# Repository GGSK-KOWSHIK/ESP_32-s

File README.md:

## Project Summary:4 Layers Custom IoT PCB with ESP32-C3-02.

This project involves the design and development of a **4-layer custom PCB** for an IoT application powered by the ESP32-C3-02 SoC. The board integrates **Wi-Fi/BLE connectivity** and **TP4056-based Li-ion charging circuitry**, enabling efficient and safe charging of a single-cell Li-ion battery.

### Key Features

- **Microcontroller**: ESP32-C3-02 SoC with Wi-Fi and BLE connectivity  
- **Power Management**: TP4056 IC for single-cell Li-ion battery charging with thermal regulation  
- **Battery Protection**: Integrated under-voltage lockout and trickle charging  
- **Sensors and Modules**:  
  - BME280 for temperature, humidity, and pressure sensing  
  - Ambient light and sound sensors  
  - Mini SD card reader for local data storage  
  - Onboard flash memory for extended storage  
- **Display**: I2C OLED for real-time data visualization  
- **Power Inputs**:  
  - USB-C connector for charging and data transfer  
  - LiPo battery connector with onboard charging circuitry  
- **Indicators**: LED indicators showing charging and full-charge status  

### Design Highlights

1. **Power Supply Integration**  
   - USB-C powers both charging and system operation  
   - TP4056 manages charging and protection  
   - Regulated supply ensures ESP32-C3-02 stability  

2. **Modular Architecture**  
   - Supports multiple onboard sensors  
   - Expandable via additional I2C devices  

3. **Safe and Efficient Charging**  
   - Programmable charging current (external resistor)  
   - Automatic charge termination and built-in protection  

4. **Compact and Reliable Layout**  
   - Optimized **4-layer PCB routing** for minimal power loss  
   - Thermal management for TP4056 and critical components  

### Applications

- IoT edge devices for environmental monitoring  
- Low-power battery-operated data logging systems  
- Prototyping platform for ESP32-based IoT solutions

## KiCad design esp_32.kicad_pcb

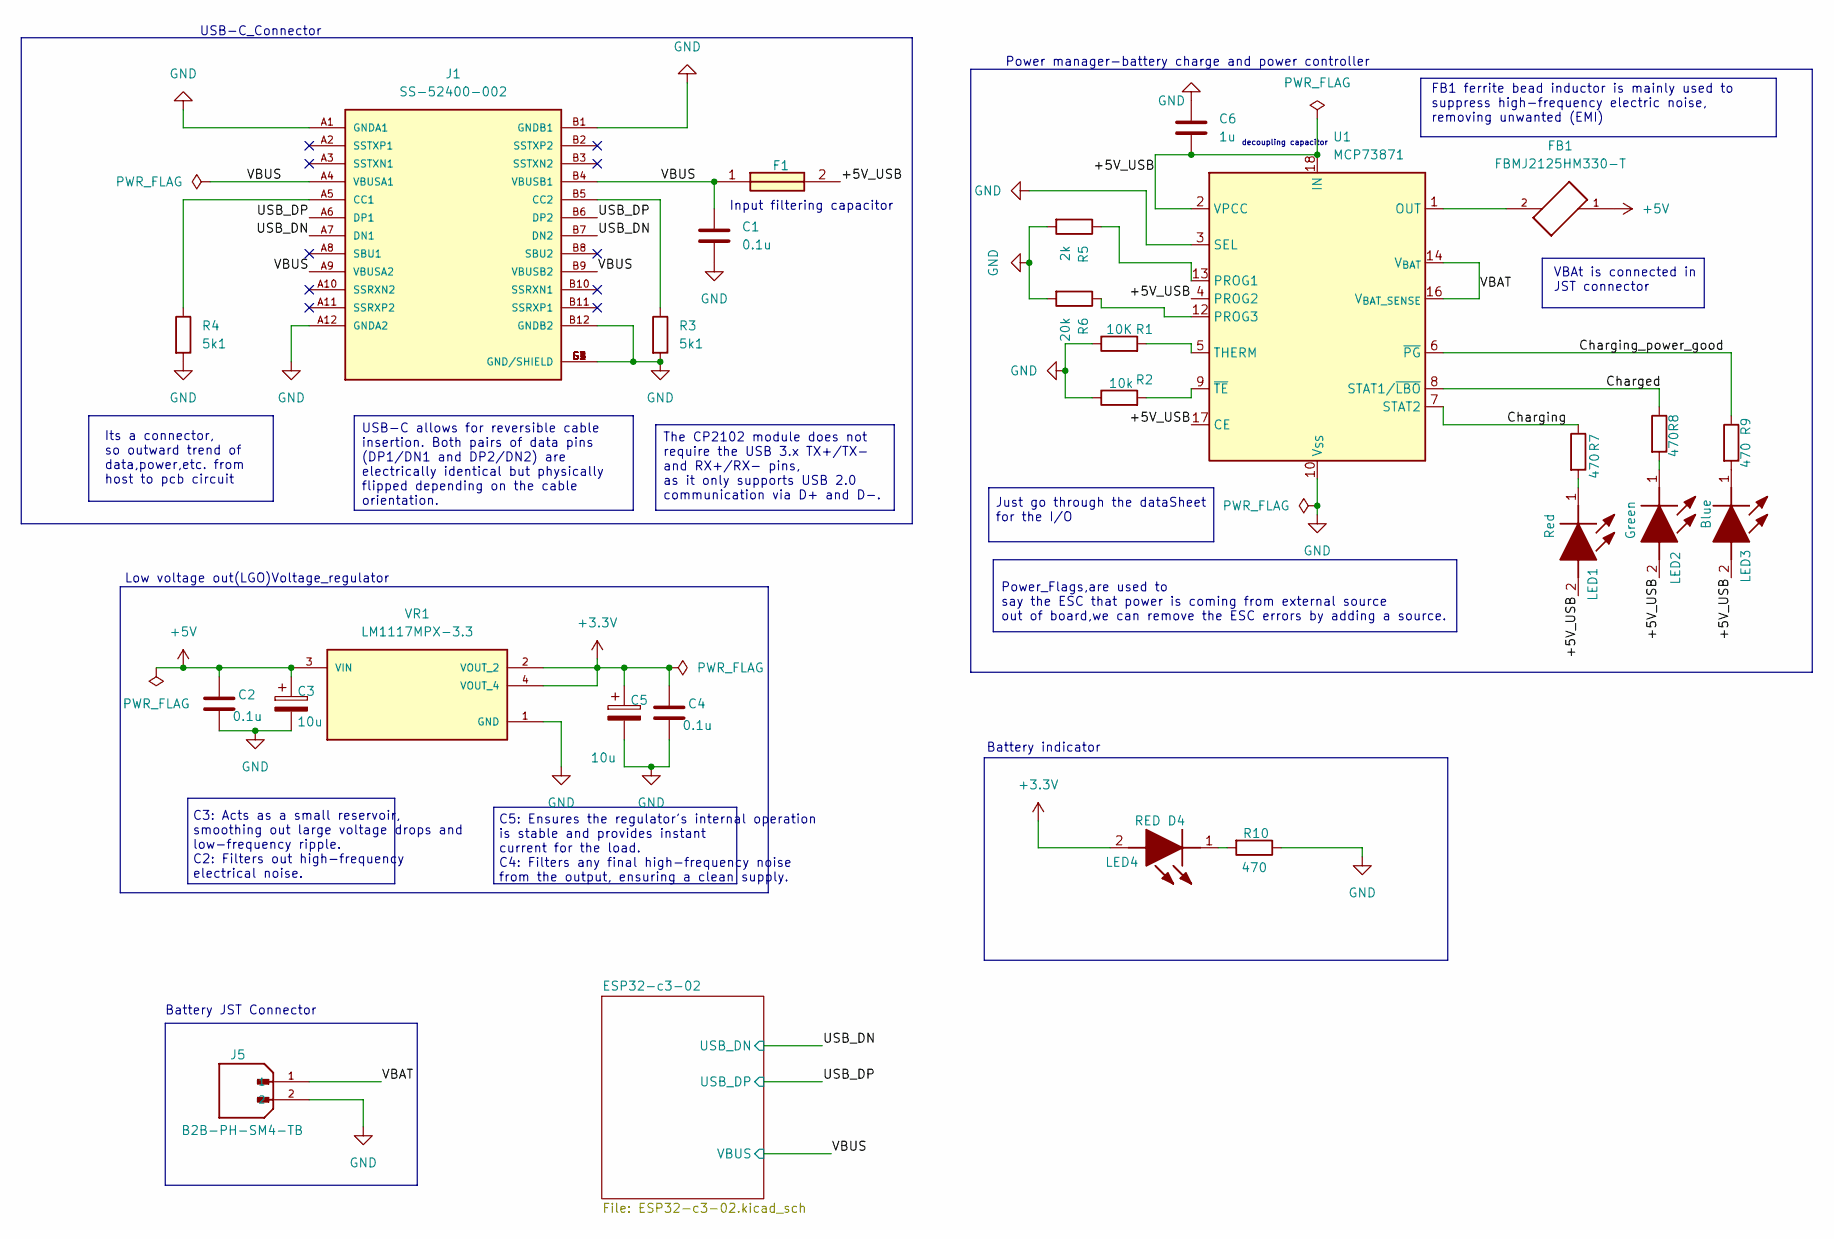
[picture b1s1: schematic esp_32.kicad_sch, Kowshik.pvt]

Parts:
C1, C2, C4: 0.1u; C_0805_2012Metric
C3, C5: 10u; T491A
C6: 1u; C_0805_2012Metric
F1: 0ZCH0110AF2E; FUSC3226X100N; Manufacturer_Part_Number 0ZCH0110AF2E
FB1: FBMJ2125HM330-T; BEADC2012X105N
J1: SS-52400-002; BELFUSE_SS-52400-002; PARTREV A0
J5: B2B-PH-SM4-TB; JST_PH_B2B-PH-K_1x02_P2.00mm_Vertical; PARTREV N/A
LED1: Red; LEDC2012X120N; Manufacturer_Part_Number LTST-C170KRKT; Mouser Part Number 859-LTST-C170KRKT
LED2: Green; LEDC2012X120N; Manufacturer_Part_Number LTST-C170GKT; Mouser Part Number 859-LTST-C170GKT
LED3: Blue; LEDC2012X120N; Manufacturer_Part_Number LTST-C170TBKT; Mouser Part Number 859-LTST-C170TBKT
LED4: RED D4; LEDC2012X120N; Manufacturer_Part_Number LTST-C170KRKT; Mouser Part Number 859-LTST-C170KRKT
R1: 10K; R_0805_2012Metric
R2: 10k; R_0805_2012Metric
R3, R4: 5k1; R_0805_2012Metric
R5: 2k; R_0805_2012Metric
R6: 20k; R_0805_2012Metric
R7, R8, R9, R10: 470; R_0805_2012Metric
U1: MCP73871; QFN-20-1EP_4x4mm_P0.5mm_EP2.5x2.5mm
VR1: LM1117MPX-3.3; VREG_LM1117MPX-3.3

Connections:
+3.3V: C4.1, C5.1, LED4.2 (A), VR1.2 (VOUT_2), VR1.4 (VOUT_4); also elsewhere on the board
+5V: C2.1, C3.1, FB1.1, VR1.3 (VIN)
/+5V_USB: C6.2, F1.2, LED1.2 (A), LED2.2 (A), LED3.2 (A), U1.2 (VPCC), U1.4 (PROG2), U1.17 (CE), U1.18 (IN), U1.19 (IN)
/Charged: R8.1, U1.8 (STAT1/~LBO)
/Charging: R7.1, U1.7 (STAT2)
/Charging_power_good: R9.1, U1.6 (~PG)
/USB_DN: J1.A7 (DN1), J1.B7 (DN2); also elsewhere on the board
/USB_DP: J1.A6 (DP1), J1.B6 (DP2); also elsewhere on the board
/VBAT: J5.1, U1.14 (V_{BAT}), U1.15 (V_{BAT}), U1.16 (V_{BAT_SENSE})
/VBUS: C1.1, F1.1, J1.A4 (VBUSA1), J1.A9 (VBUSA2), J1.B4 (VBUSB1), J1.B9 (VBUSB2); also elsewhere on the board
GND: C1.2, C2.2, C3.2, C4.2, C5.2, C6.1, J1.A1 (GNDA1), J1.A12 (GNDA2), J1.B1 (GNDB1), J1.B12 (GNDB2), J1.G1 (GND/SHIELD), J1.G2 (GND/SHIELD), J1.G3 (GND/SHIELD), J1.G4 (GND/SHIELD), J1.S1 (GND/SHIELD), J1.S2 (GND/SHIELD), J1.S3 (GND/SHIELD), J1.S4 (GND/SHIELD), J5.2, R1.1, R2.1, R3.2, R4.2, R5.2, R6.2, R10.1, U1.3 (SEL), U1.10 (V_{SS}), U1.11 (V_{SS}), U1.21 (V_{SS}), VR1.1 (GND); also elsewhere on the board
unnamed: FB1.2, U1.1 (OUT), U1.20 (OUT)
unnamed: J1.A5 (CC1), R4.1
unnamed: J1.B5 (CC2), R3.1
unnamed: LED1.1 (K), R7.2
unnamed: LED2.1 (K), R8.2
unnamed: LED3.1 (K), R9.2
unnamed: LED4.1 (K), R10.2
unnamed: R5.1, U1.13 (PROG1)
unnamed: R6.1, U1.12 (PROG3)
unnamed: R1.2, U1.5 (THERM)
unnamed: R2.2, U1.9 (~TE)

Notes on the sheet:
Input filtering capacitor
Power manager-battery charge and power controller
C3: Acts as a small reservoir, smoothing out large voltage drops and low-frequency ripple. C2: Filters out high-frequency electrical noise.
Battery indicator
Low voltage out(LGO)Voltage_regulator
Battery JST Connector
Power_Flags,are used to say the ESC that power is coming from external source out of board,we can remove the ESC errors by adding a source.
VBAt is connected in JST connector
Its a connector, so outward trend of data,power,etc. from host to pcb circuit
C5: Ensures the regulator's internal operation is stable and provides instant current for the load. C4: Filters any final high-frequency noise from the output, ensuring a clean supply.
decoupling capacitor
USB-C_Connector
Just go through the dataSheet for the I/O
FB1 ferrite bead inductor is mainly used to suppress high-frequency electric noise, removing unwanted (EMI)
USB-C allows for reversible cable insertion. Both pairs of data pins (DP1/DN1 and DP2/DN2) are electrically identical but physically flipped depending on the cable orientation.
The CP2102 module does not require the USB 3.x TX+/TX- and RX+/RX- pins, as it only supports USB 2.0 communication via D+ and D-.

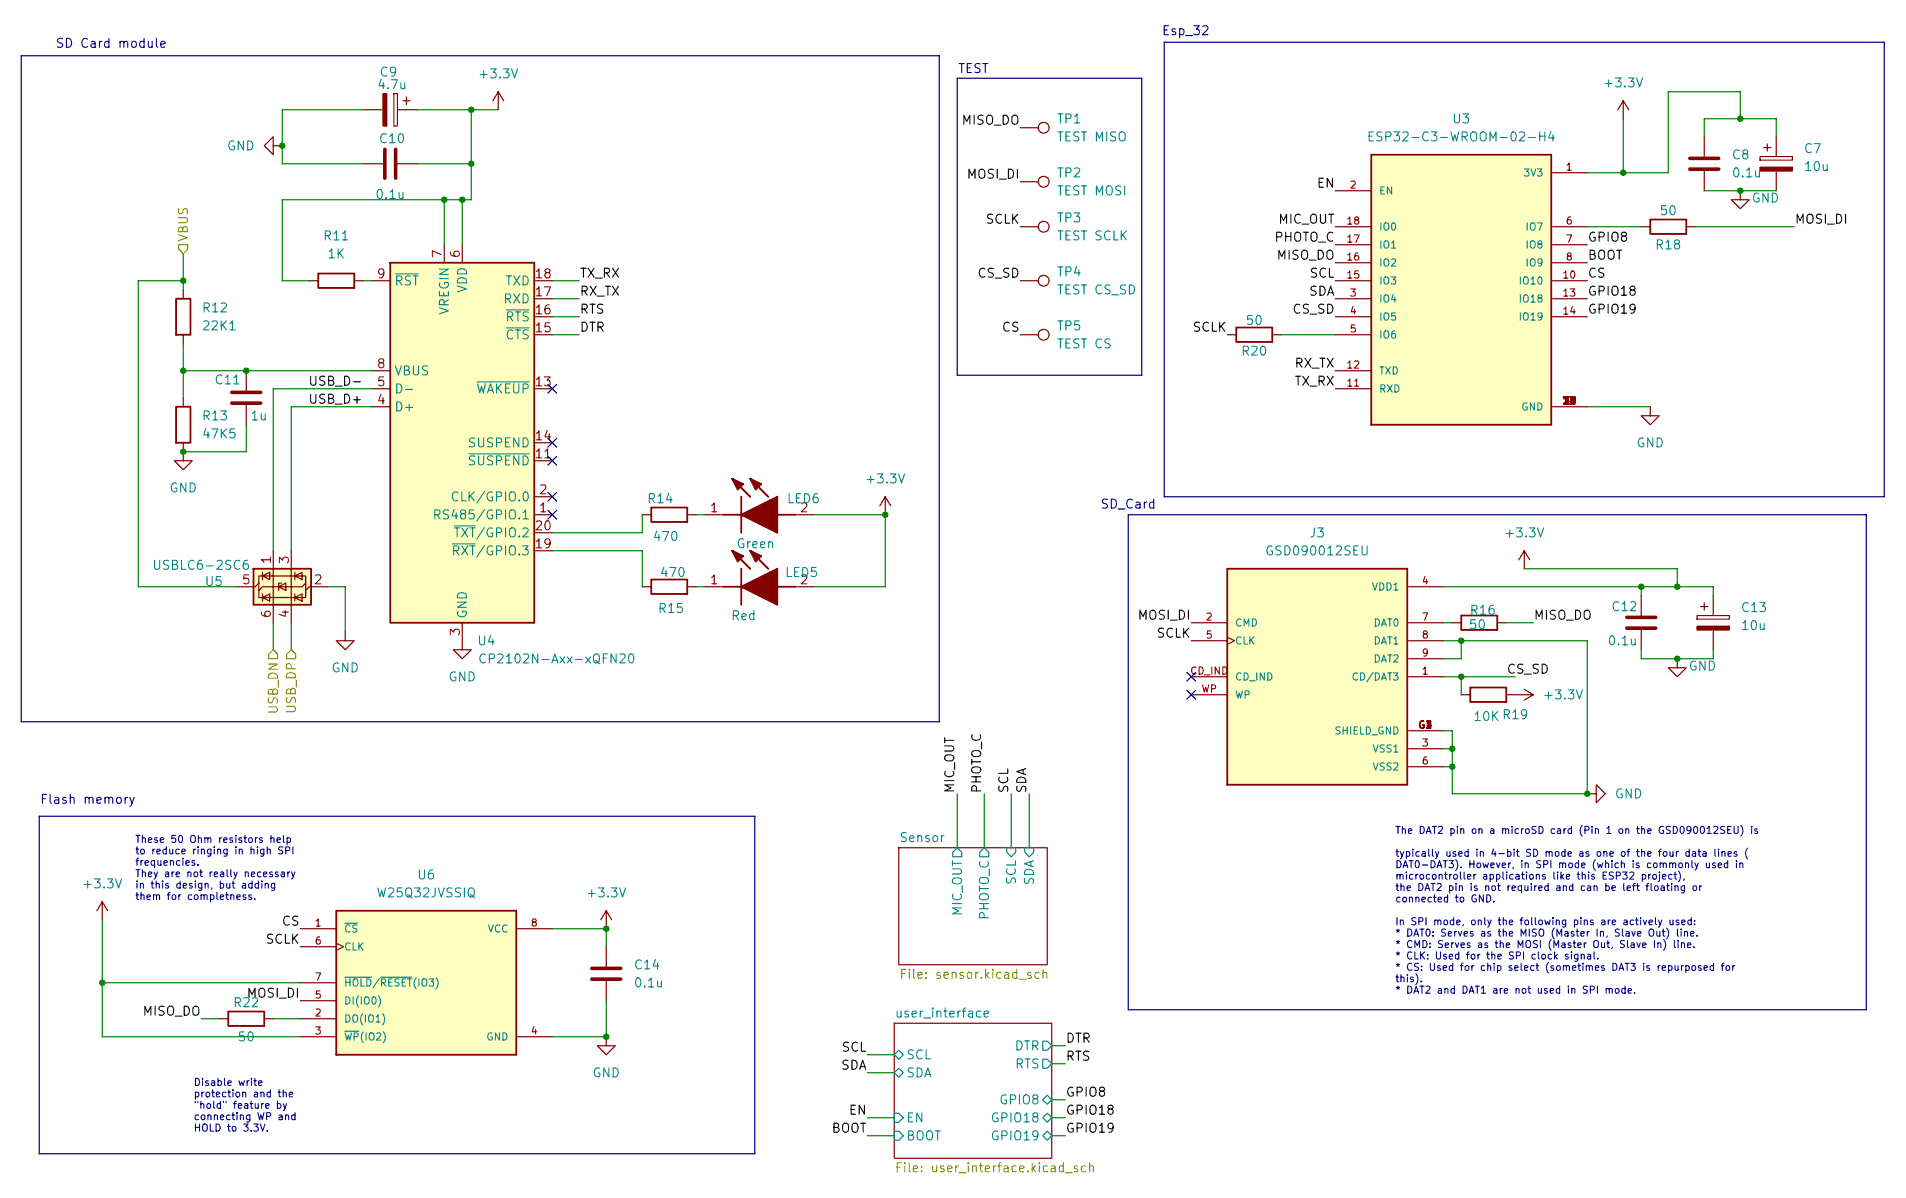
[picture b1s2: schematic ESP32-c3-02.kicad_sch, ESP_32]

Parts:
C7, C13: 10u; T491A
C8, C10, C12, C14: 0.1u; C_0805_2012Metric
C9: 4.7u; T491A
C11: 1u; C_0805_2012Metric
J3: GSD090012SEU; AMPHENOL_GSD090012SEU; PARTREV E
LED5: Red; LEDC2012X120N; Manufacturer_Part_Number LTST-C170KRKT; Mouser Part Number 859-LTST-C170KRKT
LED6: Green; LEDC2012X120N; Manufacturer_Part_Number LTST-C170GKT; Mouser Part Number 859-LTST-C170GKT
R11: 1K; R_0805_2012Metric
R12: 22K1; R_0805_2012Metric
R13: 47K5; R_0805_2012Metric
R14, R15: 470; R_0805_2012Metric
R16, R18, R20, R22: 50; R_0805_2012Metric
R19: 10K; R_0805_2012Metric
TP1: TEST MISO; TestPoint_Pad_D1.0mm
TP2: TEST MOSI; TestPoint_Pad_D1.0mm
TP3: TEST SCLK; TestPoint_Pad_D1.0mm
TP4: TEST CS_SD; TestPoint_Pad_D1.0mm
TP5: TEST CS; TestPoint_Pad_D1.0mm
U3: ESP32-C3-WROOM-02-H4; MODULE_ESP32-C3-WROOM-02-H4
U4: CP2102N-Axx-xQFN20; SiliconLabs_QFN-20-1EP_3x3mm_P0.5mm_EP1.8x1.8mm
U5: USBLC6-2SC6; SOT-23-6
U6: W25Q32JVSSIQ; SOIC127P790X216-8N; M_PART_NUMBER W25QXX

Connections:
+3.3V: C7.1, C8.1, C9.1, C10.2, C12.1, C13.1, C14.1, J3.4 (VDD1), LED5.2 (A), LED6.2 (A), R11.1, R19.2, U3.1 (3V3), U4.6 (VDD), U4.7 (VREGIN), U6.3 (~WP(IO2)), U6.7 (~HOLD/~RESET(IO3)), U6.8 (VCC); also elsewhere on the board
/ESP32-c3-02/BOOT: U3.8 (IO9); also elsewhere on the board
/ESP32-c3-02/CS: TP5.1, U3.10 (IO10), U6.1 (~CS)
/ESP32-c3-02/CS_SD: J3.1 (CD/DAT3), R19.1, TP4.1, U3.4 (IO5)
/ESP32-c3-02/DTR: U4.15 (~CTS); also elsewhere on the board
/ESP32-c3-02/EN: U3.2 (EN); also elsewhere on the board
/ESP32-c3-02/GPIO8: U3.7 (IO8); also elsewhere on the board
/ESP32-c3-02/GPIO18: U3.13 (IO18); also elsewhere on the board
/ESP32-c3-02/GPIO19: U3.14 (IO19); also elsewhere on the board
/ESP32-c3-02/MIC_OUT: U3.18 (IO0); also elsewhere on the board
/ESP32-c3-02/MISO_DO: R16.2, R22.1, TP1.1, U3.16 (IO2)
/ESP32-c3-02/MOSI_DI: J3.2 (CMD), R18.2, TP2.1, U6.5 (DI(IO0))
/ESP32-c3-02/PHOTO_C: U3.17 (IO1); also elsewhere on the board
/ESP32-c3-02/RTS: U4.16 (~RTS); also elsewhere on the board
/ESP32-c3-02/RX_TX: U3.12 (TXD), U4.17 (RXD)
/ESP32-c3-02/SCL: U3.15 (IO3); also elsewhere on the board
/ESP32-c3-02/SCLK: J3.5 (CLK), R20.1, TP3.1, U6.6 (CLK)
/ESP32-c3-02/SDA: U3.3 (IO4); also elsewhere on the board
/ESP32-c3-02/TX_RX: U3.11 (RXD), U4.18 (TXD)
/ESP32-c3-02/USB_D+: U4.4 (D+), U5.3 (I/O2)
/ESP32-c3-02/USB_D-: U4.5 (D-), U5.1 (I/O1)
/USB_DN: U5.6 (I/O1); also elsewhere on the board
/USB_DP: U5.4 (I/O2); also elsewhere on the board
/VBUS: R12.1, U5.5 (VBUS); also elsewhere on the board
GND: C7.2, C8.2, C9.2, C10.1, C11.2, C12.2, C13.2, C14.2, J3.3 (VSS1), J3.6 (VSS2), J3.8 (DAT1), J3.9 (DAT2), J3.G1 (SHIELD_GND), J3.G2 (SHIELD_GND), J3.G3 (SHIELD_GND), J3.G4 (SHIELD_GND), R13.2, U3.9 (GND), U3.19 (GND), U3.20 (GND), U3.21 (GND), U3.22 (GND), U3.23 (GND), U3.24 (GND), U3.25 (GND), U3.26 (GND), U3.27 (GND), U3.28 (GND), U3.29 (GND), U3.30 (GND), U3.31 (GND), U3.32 (GND), U3.33 (GND), U3.34 (GND), U3.35 (GND), U3.36 (GND), U3.37 (GND), U3.38 (GND), U3.39 (GND), U4.3 (GND), U4.12 (GND), U4.21 (GND), U5.2 (GND), U6.4 (GND); also elsewhere on the board
unnamed: J3.7 (DAT0), R16.1
unnamed: LED5.1 (K), R15.2
unnamed: LED6.1 (K), R14.2
unnamed: R20.2, U3.5 (IO6)
unnamed: R18.1, U3.6 (IO7)
unnamed: C11.1, R12.2, R13.1, U4.8 (VBUS)
unnamed: R11.2, U4.9 (~RST)
unnamed: R15.1, U4.19 (~RXT/GPIO.3)
unnamed: R14.1, U4.20 (~TXT/GPIO.2)
unnamed: R22.2, U6.2 (DO(IO1))

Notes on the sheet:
SD Card module
SD_Card
Esp_32
TEST
Flash memory
These 50 Ohm resistors help to reduce ringing in high SPI frequencies. They are not really necessary in this design, but adding them for completness.
The DAT2 pin on a microSD card (Pin 1 on the GSD090012SEU) is typically used in 4-bit SD mode as one of the four data lines ( DAT0-DAT3). However, in SPI mode (which is commonly used in microcontroller applications like this ESP32 project), the DAT2 pin is not required and can be left floating or c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
Disable write protection and the "hold" feature by connecting WP and HOLD to 3.3V.

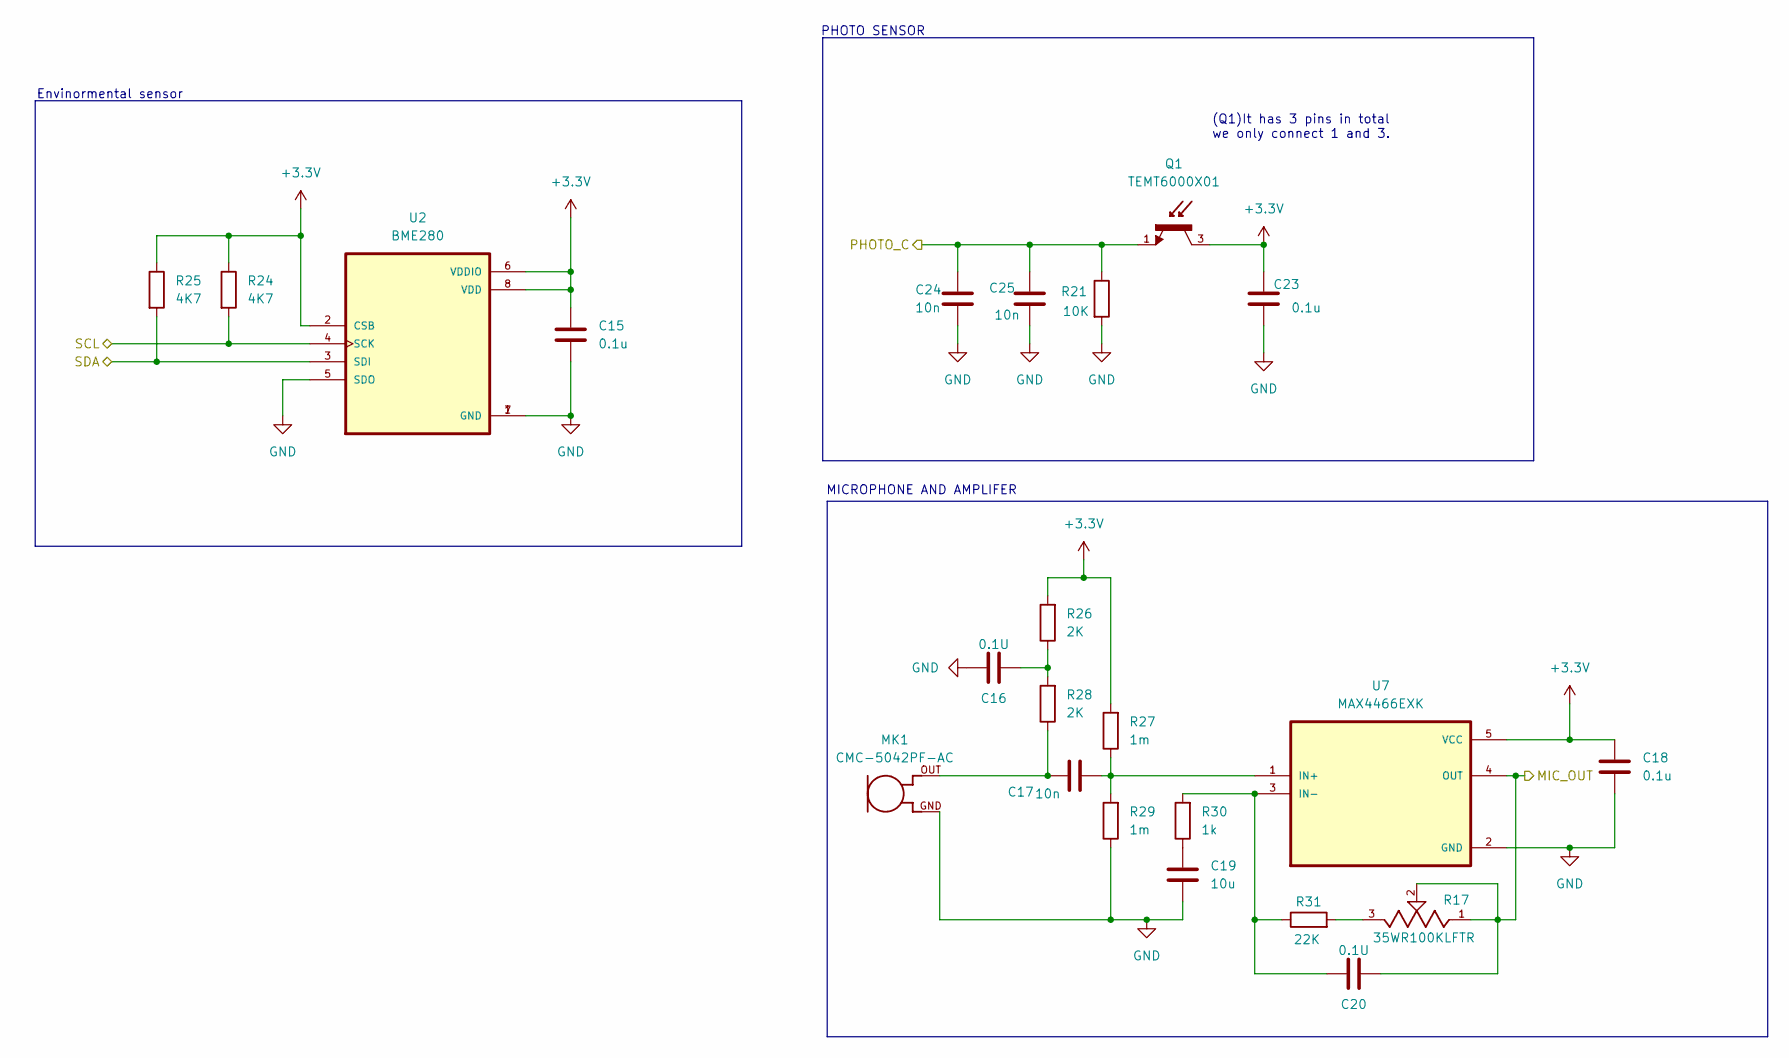
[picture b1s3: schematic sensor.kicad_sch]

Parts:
C15, C18, C23: 0.1u; C_0805_2012Metric
C16, C20: 0.1U; C_0805_2012Metric
C17, C24, C25: 10n; C_0805_2012Metric
C19: 10u; C_0805_2012Metric
MK1: CMC-5042PF-AC; CUI_CMC-5042PF-AC
Q1: TEMT6000X01; TRANS_TEMT6000X01; PARTREV 1.9
R17: 35WR100KLFTR; TRIM_35WR100KLFTR; PARTREV D
R21: 10K; R_0805_2012Metric
R24, R25: 4K7; R_0805_2012Metric
R26, R28: 2K; R_0805_2012Metric
R27, R29: 1m; R_0805_2012Metric
R30: 1k; R_0805_2012Metric
R31: 22K; R_0805_2012Metric
U2: BME280; PSON65P250X250X100-8N
U7: MAX4466EXK; SOT65P210X110-5N

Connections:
+3.3V: C15.1, C18.1, C23.1, Q1.3, R24.1, R25.1, R26.2, R27.2, U2.2 (CSB), U2.6 (VDDIO), U2.8 (VDD), U7.5 (VCC); also elsewhere on the board
/ESP32-c3-02/MIC_OUT: C20.2, R17.1, R17.2, U7.4 (OUT); also elsewhere on the board
/ESP32-c3-02/PHOTO_C: C24.1, C25.1, Q1.1, R21.1; also elsewhere on the board
/ESP32-c3-02/SCL: R24.2, U2.4 (SCK); also elsewhere on the board
/ESP32-c3-02/SDA: R25.2, U2.3 (SDI); also elsewhere on the board
GND: C15.2, C16.1, C18.2, C19.2, C23.2, C24.2, C25.2, MK1.GND, R21.2, R29.1, U2.1 (GND), U2.5 (SDO), U2.7 (GND), U7.2 (GND); also elsewhere on the board
unnamed: C16.2, R26.1, R28.2
unnamed: C17.1, MK1.OUT, R28.1
unnamed: C19.1, R30.1
unnamed: R17.3, R31.2
unnamed: C17.2, R27.1, R29.2, U7.1 (IN+)
unnamed: C20.1, R30.2, R31.1, U7.3 (IN-)

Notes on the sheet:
PHOTO SENSOR
MICROPHONE AND AMPLIFER
(Q1)It has 3 pins in total we only connect 1 and 3.
Envinormental sensor

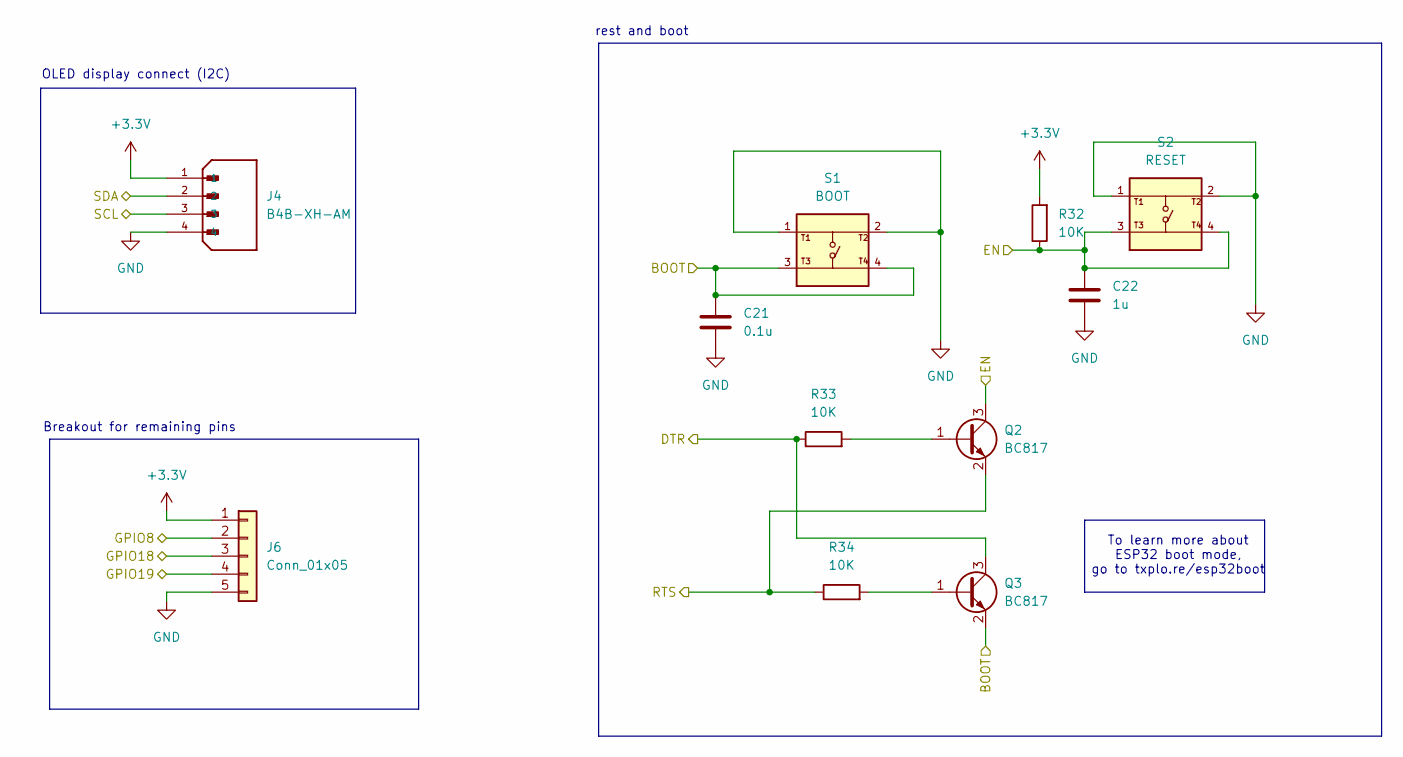
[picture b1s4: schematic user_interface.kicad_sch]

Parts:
C21: 0.1u; C_0805_2012Metric
C22: 1u; C_0805_2012Metric
J4: B4B-XH-AM; JST_B4B-XH-AM__LF__SN_; PARTREV N/A
J6: Conn_01x05; PinHeader_1x05_P2.54mm_Vertical
Q2, Q3: BC817; SOT-23
R32, R33, R34: 10K; R_0805_2012Metric
S1: BOOT; SW_USLPT2819DT2TR; PARTREV P
S2: RESET; SW_USLPT2819DT2TR; PARTREV P

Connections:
+3.3V: J4.1, J6.1, R32.2; also elsewhere on the board
/ESP32-c3-02/BOOT: C21.1, Q3.2 (E), S1.3, S1.4; also elsewhere on the board
/ESP32-c3-02/DTR: Q3.3 (C), R33.1; also elsewhere on the board
/ESP32-c3-02/EN: C22.1, Q2.3 (C), R32.1, S2.3, S2.4; also elsewhere on the board
/ESP32-c3-02/GPIO8: J6.2; also elsewhere on the board
/ESP32-c3-02/GPIO18: J6.3; also elsewhere on the board
/ESP32-c3-02/GPIO19: J6.4; also elsewhere on the board
/ESP32-c3-02/RTS: Q2.2 (E), R34.1; also elsewhere on the board
/ESP32-c3-02/SCL: J4.3; also elsewhere on the board
/ESP32-c3-02/SDA: J4.2; also elsewhere on the board
GND: C21.2, C22.2, J4.4, J6.5, S1.1, S1.2, S2.1, S2.2; also elsewhere on the board
unnamed: Q2.1 (B), R33.2
unnamed: Q3.1 (B), R34.2

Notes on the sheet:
OLED display connect (I2C)
rest and boot
Breakout for remaining pins
To learn more about ESP32 boot mode, go to txplo.re/esp32boot

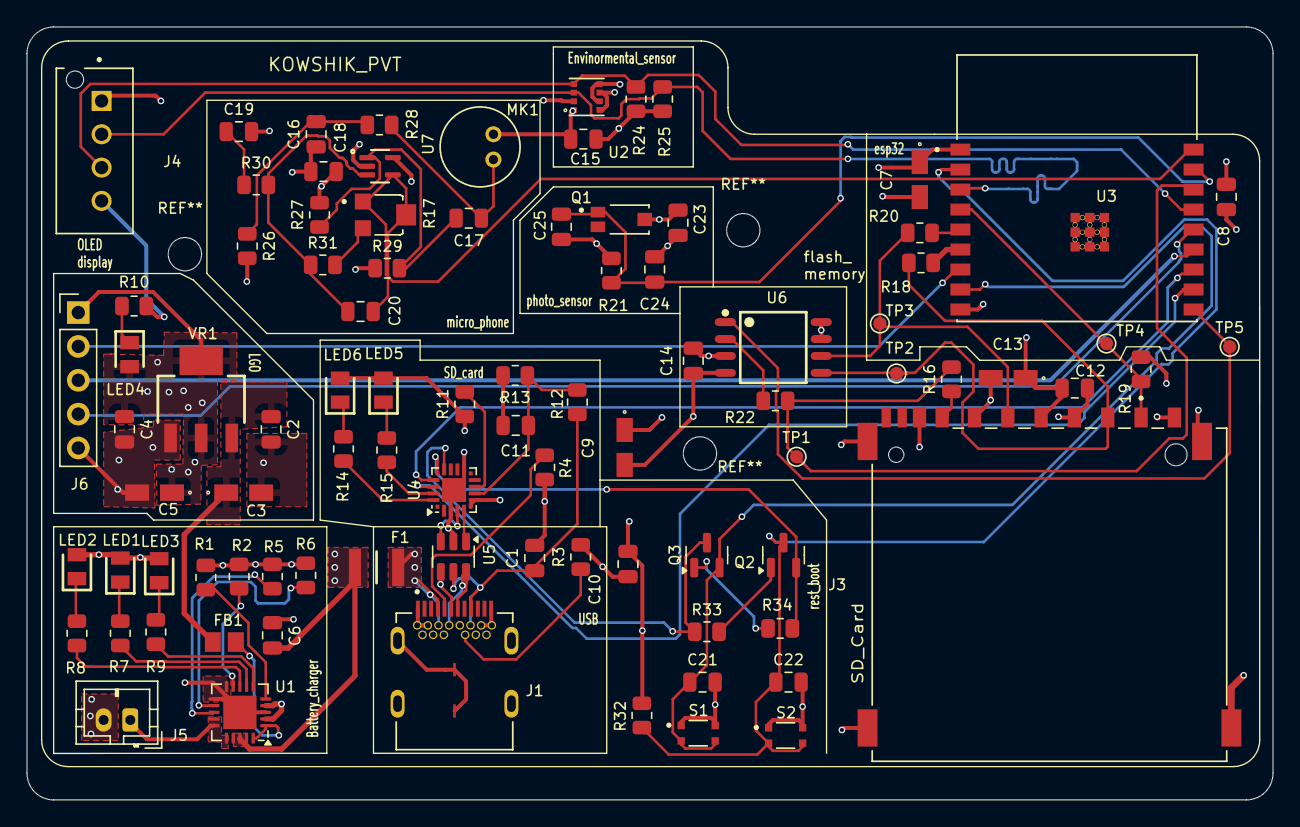
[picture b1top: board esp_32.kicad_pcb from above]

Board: 4 copper layers, 93.5 x 58.0 mm, 90 parts (0 on the bottom side), 60 nets.

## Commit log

2025-09-18 schematic
2025-09-21 schematic1
2025-09-23 intial_PCB
2025-09-23 PCB1
2025-09-24 finished_PCB
2025-09-24 images
2025-09-27 finial
2025-09-27 image
